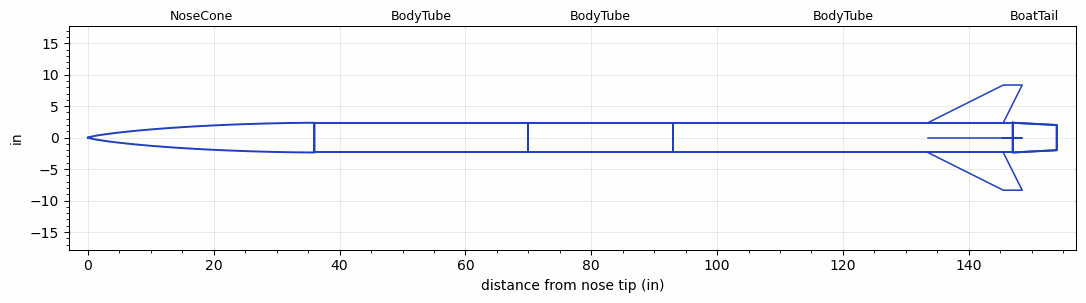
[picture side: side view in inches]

<RASAeroDocument>
 <FileVersion>2</FileVersion>
 <RocketDesign>
  <NoseCone>
   <Length>36</Length>
   <Diameter>4.7244</Diameter>
   <Shape>LV-Haack</Shape>
   <Location>0</Location>
  </NoseCone>
  <BodyTube>
   <Length>34</Length>
   <Diameter>4.7244</Diameter>
   <Location>36</Location>
  </BodyTube>
  <BodyTube>
   <Length>23</Length>
   <Diameter>4.7244</Diameter>
   <Location>70</Location>
  </BodyTube>
  <BodyTube>
   <Length>54</Length>
   <Diameter>4.7244</Diameter>
   <Location>93</Location>
   <BoattailLength>7</BoattailLength>
   <BoattailRearDiameter>4</BoattailRearDiameter>
   <Fin>
    <Count>4</Count>
    <Chord>12</Chord>
    <Span>6</Span>
    <SweepDistance>12</SweepDistance>
    <TipChord>3</TipChord>
    <Thickness>0.3</Thickness>
    <LERadius>0.025</LERadius>
    <Location>13.5</Location>
    <AirfoilSection>Double Wedge</AirfoilSection>
    <FX1>6</FX1>
   </Fin>
  </BodyTube>
  <BoatTail>
   <Length>7</Length>
   <Diameter>4.7244</Diameter>
   <RearDiameter>4</RearDiameter>
   <Location>147</Location>
  </BoatTail>
  <Surface>Camouflage Paint</Surface>
  <ModifiedBarrowman>False</ModifiedBarrowman>
  <Turbulence>False</Turbulence>
  <UseBooster1>False</UseBooster1>
  <UseBooster2>False</UseBooster2>
 </RocketDesign>
 <LaunchSite>
  <Altitude>0</Altitude>
  <Pressure>0</Pressure>
  <RodAngle>0</RodAngle>
  <RodLength>4</RodLength>
  <Temperature>74</Temperature>
  <WindSpeed>0</WindSpeed>
 </LaunchSite>
 <Recovery>
  <Altitude1>1000</Altitude1>
  <Altitude2>1000</Altitude2>
  <DeviceType1>None</DeviceType1>
  <DeviceType2>None</DeviceType2>
  <Event1>False</Event1>
  <Event2>False</Event2>
  <Size1>1</Size1>
  <Size2>1</Size2>
  <EventType1>None</EventType1>
  <EventType2>None</EventType2>
  <CD1>1.33</CD1>
  <CD2>1.33</CD2>
 </Recovery>
 <SimulationList>
  <Simulation>
   <SustainerEngine>M1340W  (AT)</SustainerEngine>
   <SustainerLaunchWt>52.25</SustainerLaunchWt>
   <SustainerNozzleDiameter>2</SustainerNozzleDiameter>
   <SustainerCG>102</SustainerCG>
   <SustainerIgnitionDelay>0</SustainerIgnitionDelay>
   <Booster1SeparationDelay>0</Booster1SeparationDelay>
   <Booster1IgnitionDelay>0</Booster1IgnitionDelay>
   <IncludeBooster1>False</IncludeBooster1>
   <Booster2Delay>0</Booster2Delay>
   <IncludeBooster2>False</IncludeBooster2>
   <TimetoApogee>22.91043</TimetoApogee>
   <MaxAltitude>8554.831</MaxAltitude>
   <MaxVelocity>811.322</MaxVelocity>
   <OptimumWt>33.96251</OptimumWt>
   <OptimumMaxAlt>33.96251</OptimumMaxAlt>
  </Simulation>
  <Simulation>
   <SustainerEngine>M1340W  (AT)</SustainerEngine>
   <SustainerLaunchWt>52.25</SustainerLaunchWt>
   <SustainerNozzleDiameter>2</SustainerNozzleDiameter>
   <SustainerCG>102</SustainerCG>
   <SustainerIgnitionDelay>0</SustainerIgnitionDelay>
   <Booster1SeparationDelay>0</Booster1SeparationDelay>
   <Booster1IgnitionDelay>0</Booster1IgnitionDelay>
   <IncludeBooster1>False</IncludeBooster1>
   <Booster2Delay>0</Booster2Delay>
   <IncludeBooster2>False</IncludeBooster2>
   <TimetoApogee>25.63049</TimetoApogee>
   <MaxAltitude>10245.13</MaxAltitude>
   <MaxVelocity>850.7471</MaxVelocity>
  </Simulation>
 </SimulationList>
</RASAeroDocument>
